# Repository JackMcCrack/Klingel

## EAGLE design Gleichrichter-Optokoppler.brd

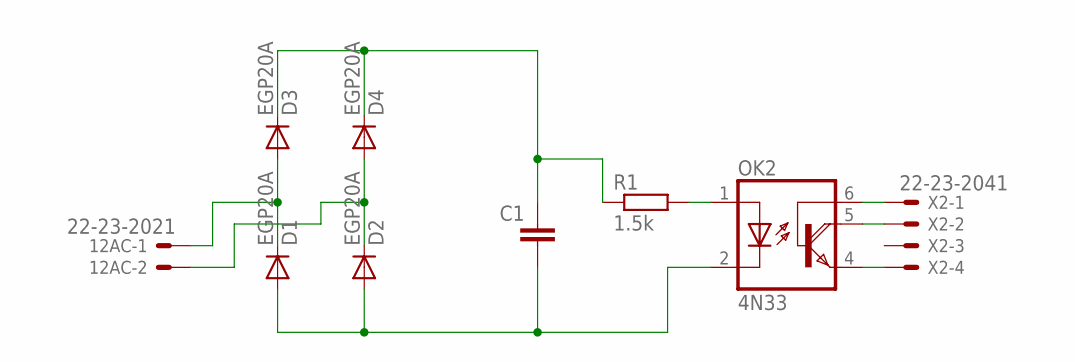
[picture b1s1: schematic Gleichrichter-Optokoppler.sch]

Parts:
12AC: 22-23-2021
C1: C5/4.5; C5B4.5
D1, D2, D3, D4: EGP20A; DO15-12
OK2: 4N33; DIL06
R1: 1.5k; 0207/10
X2: 22-23-2041

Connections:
unnamed: 12AC.1, D1.C, D3.A
unnamed: 12AC.2, D2.C, D4.A
unnamed: C1.2, D1.A, D2.A, OK2.2 (C)
unnamed: C1.1, D3.C, D4.C, R1.1
unnamed: OK2.1 (A), R1.2
unnamed: OK2.6 (B), X2.1
unnamed: OK2.5 (COL), X2.2
unnamed: OK2.4 (E), X2.4

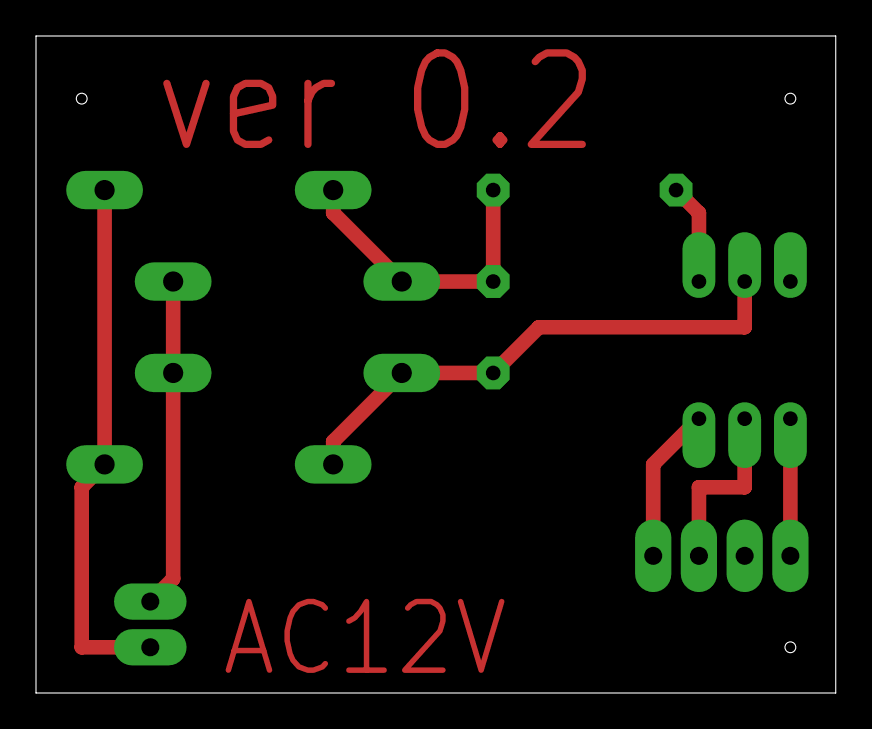
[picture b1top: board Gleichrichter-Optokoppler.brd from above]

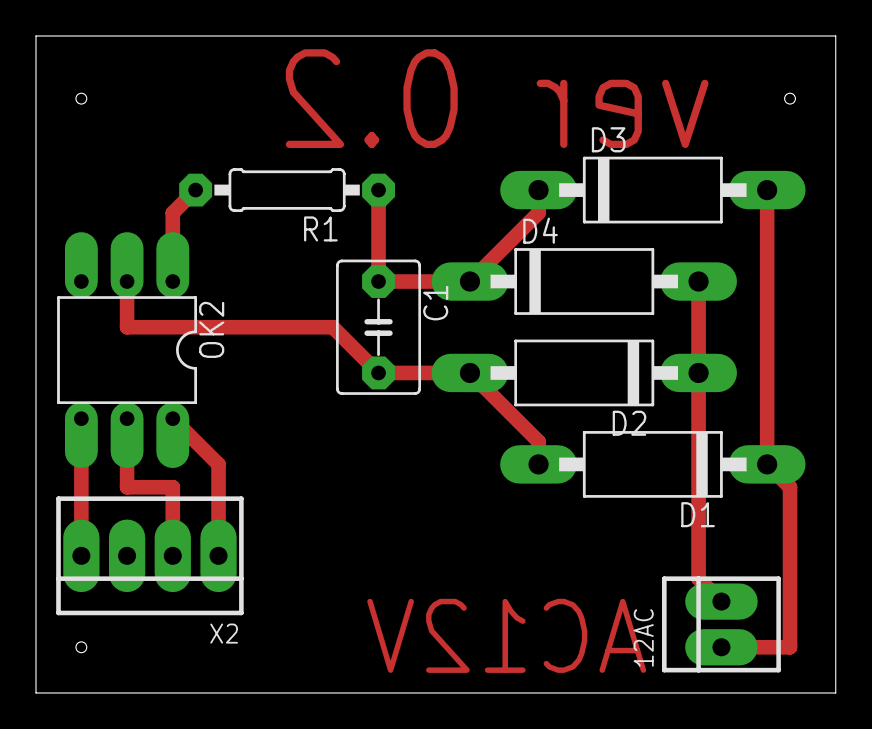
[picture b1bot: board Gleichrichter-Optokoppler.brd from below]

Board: 2 copper layers, 44.4 x 36.5 mm, 9 parts (9 on the bottom side), 8 nets.

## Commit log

2015-03-05 redesign des Boards
2015-03-05 datasheet of 4N38A and powersupply text
